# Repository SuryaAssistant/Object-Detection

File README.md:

# Object-Detection
Pendeteksian Objek Menggunakan Metode Deteksi Warna Model HSV

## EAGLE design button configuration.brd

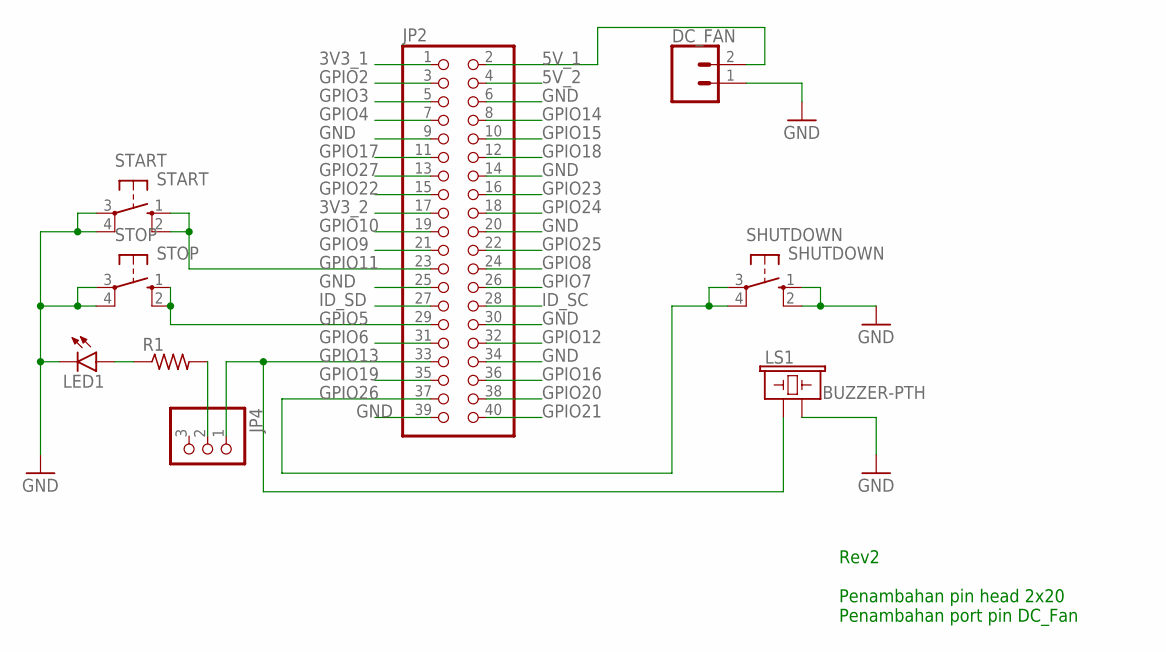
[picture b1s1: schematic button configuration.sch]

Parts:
DC_FAN: CONN_02; 1X02
JP2: PINHD-2X20-BIG; 2X20-BIG
JP4: PINHD-1X3; 1X03
LED1: LED5MM
LS1: BUZZER-PTH; BUZZER-12MM
R1: R-US_0207/10; 0207/10
SHUTDOWN: SHUTDOWN; B3F-40XX
START: START; B3F-40XX
STOP: STOP; B3F-40XX

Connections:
3V3_1: JP2.1
3V3_2: JP2.17
5V_1: DC_FAN.2, JP2.2
5V_2: JP2.4
GND: DC_FAN.1, JP2.6, JP2.9, JP2.14, JP2.20, JP2.25, JP2.30, JP2.34, JP2.39, LED1.K (C), LS1.- (2), SHUTDOWN.1 (S), SHUTDOWN.2 (S1), START.3, START.4 (P1), STOP.3, STOP.4 (P1)
GPIO2: JP2.3
GPIO3: JP2.5
GPIO4: JP2.7
GPIO5: JP2.29, STOP.1 (S), STOP.2 (S1)
GPIO6: JP2.31
GPIO7: JP2.26
GPIO8: JP2.24
GPIO9: JP2.21
GPIO10: JP2.19
GPIO11: JP2.23, START.1 (S), START.2 (S1)
GPIO12: JP2.32
GPIO13: JP2.33, JP4.1, LS1.+ (1)
GPIO14: JP2.8
GPIO15: JP2.10
GPIO16: JP2.36
GPIO17: JP2.11
GPIO18: JP2.12
GPIO19: JP2.35
GPIO20: JP2.38
GPIO21: JP2.40
GPIO22: JP2.15
GPIO23: JP2.16
GPIO24: JP2.18
GPIO25: JP2.22
GPIO26: JP2.37, SHUTDOWN.3, SHUTDOWN.4 (P1)
GPIO27: JP2.13
ID_SC: JP2.28
ID_SD: JP2.27
unnamed: LED1.A, R1.1
unnamed: JP4.2, R1.2

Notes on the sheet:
Rev2 Penambahan pin head 2x20 Penambahan port pin DC_Fan

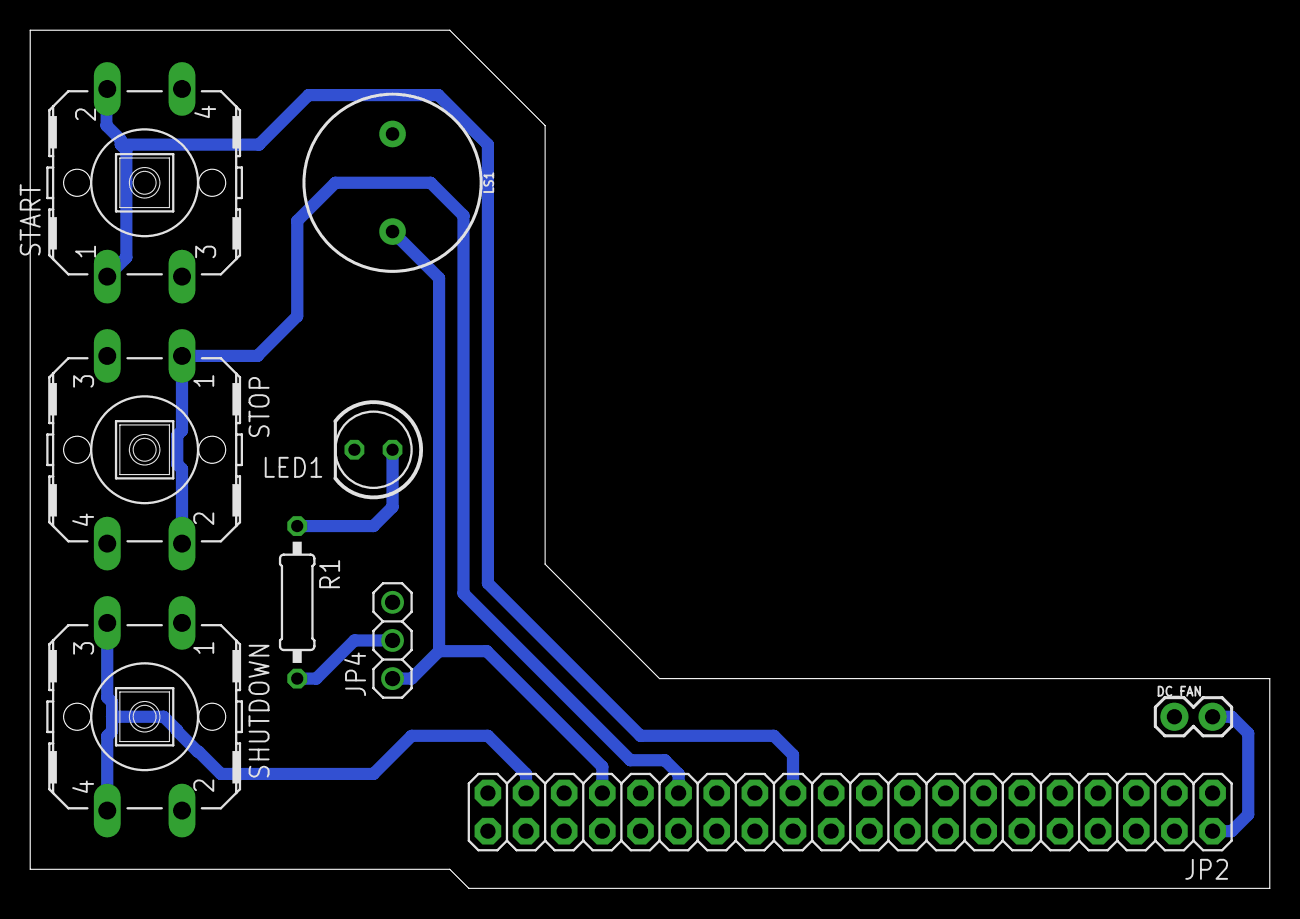
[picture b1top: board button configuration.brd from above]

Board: 2 copper layers, 82.5 x 57.1 mm, 9 parts (0 on the bottom side), 8 nets.

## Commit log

2020-05-31 Create start_detection
2020-05-31 Create ball_tracking
2020-05-31 Rename ball_tracking to ball_tracking.py
2020-05-31 Rename start_detection to start_detection.py
2020-06-02 Update start_detection.py
    changing the code

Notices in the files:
parts and their libraries:
SparkFun-Electromechanical: Licensing: Creative Commons ShareAlike 4.0 International - https://creativecommons.org/licenses/by-sa/4.0
